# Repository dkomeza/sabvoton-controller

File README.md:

# sabvoton-controller

A controller for the sabvoton ebike esc.

## Pinout reference

```
---------------------------------------------------
| 01 | 02 | 03 | 04 | 05 | 06 | 07 | 08 | 09 | 10 |
---------------------------------------------------
| 11 | 12 | 13 | 14 | 15 | 16 | 17 | 18 | 19 | 20 |
---------------------------------------------------
| 21 | 22 | 23 | 24 | 25 | 26 | 27 | 28 | 29 | 30 |
---------------------------------------------------
```

- 01: speed (0V - Battery voltage)
- 02: programming (brown-blue)
- 03: low speed (controlled by gnd)
- 04: high speed (controlled by gnd)
- 05: brake (controlled by gnd)
- 06: service (unused)
- 07: empty
- 08: 5V
- 09: 5V square hall sensor (speedometer)
- 10: empty
- 11: battery voltage
- 12: programming (blue-yellow)
- 13: programming (green-black)
- 14: programming (red-black)
- 15: brake (controlled by 12v)
- 16: reverse (controlled by gnd)
- 17: gnd
- 18: gnd
- 19: throttle (0V - 5V)?
- 20: ignition (controlled by battery voltage)
- 21: engine phase (anti-theft)
- 22: empty
- 23: regen (controlled by gnd)
- 24: soft-start (connected to 26)
- 25: cruise control (controlled by gnd)
- 26: soft-start (connected to 24)
- 27: gnd
- 28: gnd
- 29: alarm (controlled by gnd)
- 30: service (unused)

## Working with the controller

### Connectors

- [x] 1: programming connector (same as the original)
- [x] 2: usb connector (for programming the arduino)

### Functions:

- [x] 1: set current gear (low, mid, high) - pins 03, 04
- [x] 2: set motor power based on the torque sensor input - pin 19
- [x] 3: read battery voltage - pin 11
- [x] 4: turn controller on/off - pin 20
- [x] 5: enable/disable soft start - pins 24, 26
- [x] 6: get engine temperature - white wire
- [x] 7: get engine rpm - white wire
- [x] 8: get controller temperature - additional sensor
- [x] 9: get battery temperature - additional sensor
- [x] 10: send data to the display - additional display
- [x] 11: get data from the display - additional display

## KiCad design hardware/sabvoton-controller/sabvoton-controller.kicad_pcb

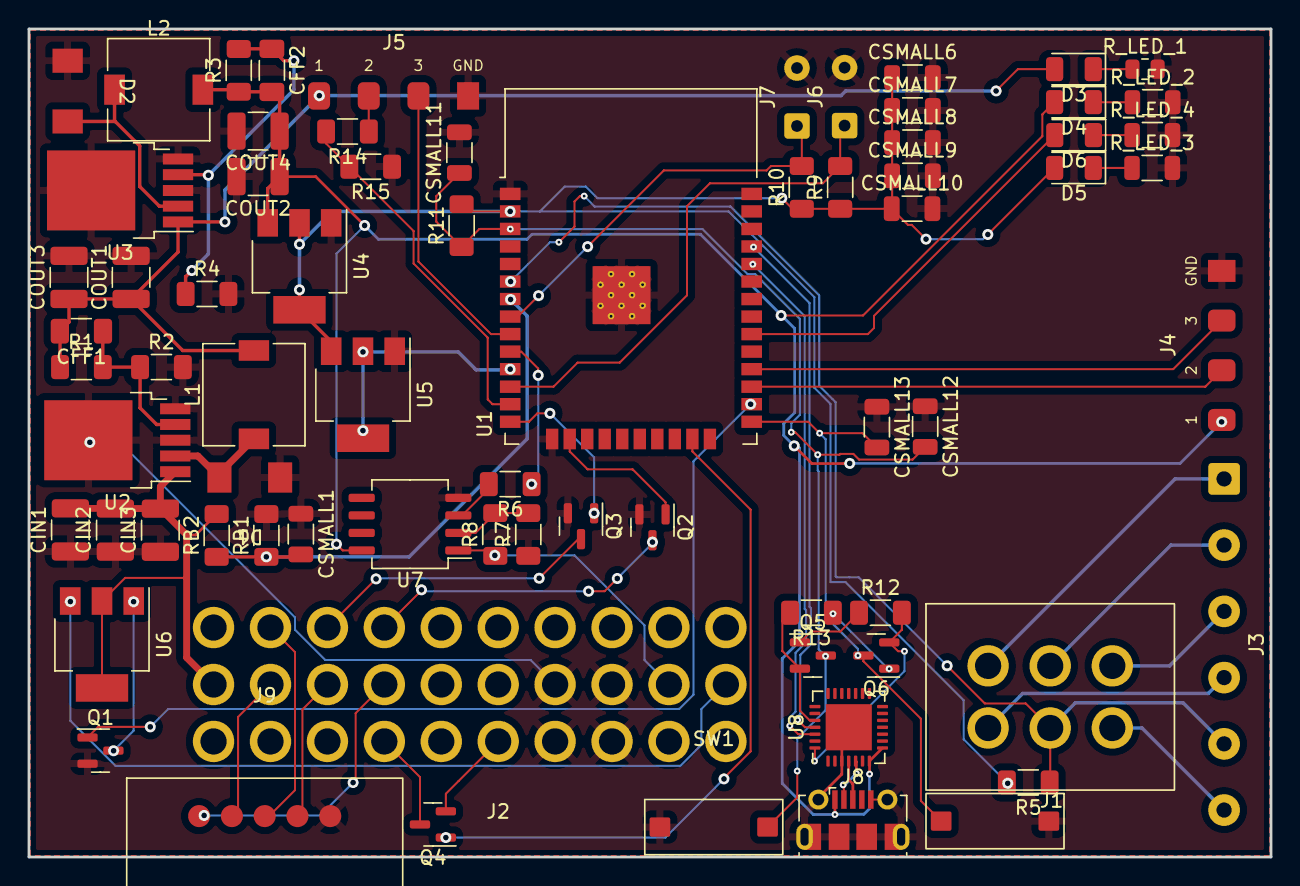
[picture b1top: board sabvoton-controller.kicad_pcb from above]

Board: 2 copper layers, 90.0 x 60.0 mm, 72 parts (0 on the bottom side), 57 nets.

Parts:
CFF1, CFF2: C; C_1206_3216Metric_Pad1.33x1.80mm_HandSolder
CIN1, CIN2, CIN3: C; C_1210_3225Metric_Pad1.33x2.70mm_HandSolder
COUT1, COUT2, COUT3, COUT4: C; C_1210_3225Metric_Pad1.33x2.70mm_HandSolder
CSMALL1, CSMALL6, CSMALL7, CSMALL8, CSMALL9, CSMALL10, CSMALL11, CSMALL12, CSMALL13: C; C_1206_3216Metric
D1, D2: S310; S2M
D3: 12V; LED_1206_3216Metric
D4: 5V; LED_1206_3216Metric
D5: 3.3V; LED_1206_3216Metric
D6: ESP_ON; LED_1206_3216Metric
J1: CONTROLLER_HALL; HALL_2x6
J2: CONN_MAIN; MAIN_3x10
J3: ENGINE_HALL; SolderWire-0.5sqmm_1x06_P4.8mm_D0.9mm_OD2.3mm
J4: DISPLAY_CONNECTOR; SolderWire-1x4-buttons
J5: TORQUE_SENSOR_CONNECTOR; SolderWire-1x4-buttons
J6: CONTROLLER_THERMISTOR_CONNECTOR; SolderWire-0.25sqmm_1x02_P4.2mm_D0.65mm_OD1.7mm
J7: BATTERY_THERMISTOR_CONNECTOR; SolderWire-0.25sqmm_1x02_P4.2mm_D0.65mm_OD1.7mm
J8: USB_B_Micro; USB_Micro-B_Molex-105017-0001
J9: PROGRAMMING_CONN; Pogramming_1x5
L1, L2: L; L_7.3x7.3_H3.5
Q1, Q2, Q3, Q4: BSS123; SOT-23
Q5, Q6: MMBT3904; SOT-23
R1: 86K; R_1206_3216Metric_Pad1.30x1.75mm_HandSolder
R2, R4, R5, R6, R9, R10, R11, R12, R13, R15: 10K; R_1206_3216Metric_Pad1.30x1.75mm_HandSolder
R3: 30K; R_1206_3216Metric_Pad1.30x1.75mm_HandSolder
R7, R8: 1K; R_1206_3216Metric_Pad1.30x1.75mm_HandSolder
R14: 33K; R_1206_3216Metric_Pad1.30x1.75mm_HandSolder
RB1: 56k; R_1206_3216Metric_Pad1.30x1.75mm_HandSolder
RB2: 1M; R_1206_3216Metric_Pad1.30x1.75mm_HandSolder
R_LED_1: 600; R_0805_2012Metric
R_LED_2: 130; R_1206_3216Metric
R_LED_3, R_LED_4: 20; R_1206_3216Metric
SW1, SW2: SW_Push; BUTTON_SW
U1: ESP32-WROOM-32
U2: BUCK_12V; TO-252-5_TabPin3
U3: BUCK_5V; TO-252-5_TabPin3
U4: NCP1117-3.3_SOT223; SOT-223-3_TabPin2
U5: LM1117-1.8; SOT-223-3_TabPin2
U6: BTS4140N; SOT-223-3_TabPin2
U7: LM358; SO-8_5.3x6.2mm_P1.27mm
U8: CP2102N-Axx-xQFN28; QFN-28-1EP_5x5mm_P0.5mm_EP3.35x3.35mm

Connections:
1.8V: U1.11 (IO26), U5.2 (VO)
3.3V: CSMALL6.1, CSMALL7.1, CSMALL8.1, CSMALL9.1, CSMALL10.1, D5.2 (A), R5.2, R9.1, R10.1, R11.2, U1.2 (VDD), U4.2 (VO), U5.3 (VI)
5V: CFF2.2, COUT2.1, COUT4.1, D4.2 (A), J4.1, J8.1 (VBUS), L2.2, R3.1, U4.3 (VI), U7.8 (VCC), U8.7 (VREGIN), U8.8 (VBUS)
12V: CFF1.2, COUT1.1, COUT3.1, D3.2 (A), J5.1, L1.2, R1.1, U3.1 (VIN)
B+: CIN1.2, CIN2.2, CIN3.2, J2.11, RB2.2, U2.1 (VIN), U6.2 (Vbb)
B-: CIN1.1, CIN2.1, CIN3.1, COUT1.2, COUT2.2, COUT3.2, COUT4.2, CSMALL1.1, CSMALL6.2, CSMALL7.2, CSMALL8.2, CSMALL9.2, CSMALL10.2, CSMALL11.2, CSMALL12.1, CSMALL13.1, D1.2 (A2), D2.2 (A2), J2.17, J2.18, J2.27, J2.28, J4.4, J5.4, J6.2, J7.2, J8.5 (GND), J8.6 (Shield), J9.5, Q1.2 (S), Q2.2 (S), Q3.2 (S), R2.2, R4.2, R7.1, R15.1, RB1.2, R_LED_1.2, R_LED_2.2, R_LED_3.2, R_LED_4.2, SW1.1, SW2.1, U1.1 (GND), U1.15 (GND), U1.38 (GND), U1.39 (GND), U2.3 (GND), U2.5 (EN), U3.3 (GND), U3.5 (EN), U4.1 (GND), U5.1 (GND), U7.4 (GND), U8.3 (GND), U8.29 (GND)
BATTERY_TEMP: J7.1, R10.2, U1.8 (IO32)
BATTERY_VOLTAGE: CSMALL1.2, RB1.1, RB2.1, U1.7 (IO35)
BOOT: CSMALL13.2, Q6.3 (C), SW2.2, U1.25 (IO0)
CONTROLLER_TEMP: J6.1, R9.2, U1.12 (IO27)
DISPLAY_RX: J4.2, U1.27 (IO16)
DISPLAY_TX: J4.3, U1.28 (IO17)
EN: CSMALL11.1, CSMALL12.2, Q5.3 (C), R11.1, SW1.2, U1.3 (EN)
ENGINE_SENSOR: J1.5, J3.5, R5.1, U1.6 (IO34)
GEAR_HIGH: J2.4, Q2.3 (D)
GEAR_LOW: J2.3, Q3.3 (D)
IGNITION: J2.20, U6.3 (OUT)
LED_ON: D6.2 (A), U1.30 (IO18)
unnamed: CFF1.1, R1.2, R2.1, U2.4 (FB)
unnamed: CFF2.1, R3.2, R4.1, U3.4 (FB)
unnamed: D1.1 (A1), L1.1, U2.2 (SW)
unnamed: D2.1 (A1), L2.1, U3.2 (SW)
unnamed: D3.1 (K), R_LED_1.1
unnamed: D4.1 (K), R_LED_2.1
unnamed: D5.1 (K), R_LED_3.1
unnamed: D6.1 (K), R_LED_4.1
unnamed: J1.1, J3.1
unnamed: J1.2, J3.2
unnamed: J1.3, J3.3
unnamed: J1.4, J3.4
unnamed: J1.6, J3.6
unnamed: J8.2 (D-), U8.5 (D-)
unnamed: J8.3 (D+), U8.4 (D+)
unnamed: Q1.3 (D), U6.1 (IN)
unnamed: Q5.1 (B), R12.1
unnamed: Q5.2 (E), R13.2, U8.24 (~RTS)
unnamed: Q6.1 (B), R13.1
unnamed: Q6.2 (E), R12.2, U8.28 (~DTR)
unnamed: R6.2, U7.3 (IN_A_+)
unnamed: R7.2, R8.2, U7.2 (IN_A_-)
PAS_SIGNAL: J5.2, R14.1
PAS_SIGNAL_LOW: R14.2, R15.2, U1.13 (IO14)
POWER_SWITCH: Q1.1 (G), U1.26 (IO4)
PROGRAMMING_BB: J2.2, J9.3
PROGRAMMING_BY: J2.12, J9.2
PROGRAMMING_GB: J2.13, J9.4
PROGRAMMING_RB: J2.14, J9.1
RXD: U1.35 (TXD0/IO1), U8.25 (RXD)
SOFT_START_A: J2.24, Q4.3 (D)
SOFT_START_B: J2.26, Q4.2 (S)
SWITCH_HIGH: Q2.1 (G), U1.16 (IO13)
SWITCH_LOW: Q3.1 (G), U1.14 (IO12)
SWITCH_SOFT_START: Q4.1 (G), U1.23 (IO15)
THROTTLE: J2.19, R8.1, U7.1 (OUT_A)
THROTTLE_OUTPUT: R6.1, U1.10 (IO25)
TORQUE_OUTPUT: J5.3, U1.9 (IO33)
TXD: U1.34 (RXD0/IO3), U8.26 (TXD)

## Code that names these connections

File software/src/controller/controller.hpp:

#ifndef CONTROLLER_H
#define CONTROLLER_H

#include <Arduino.h>

#include "../data/data.hpp"
#include "../settings/settings.hpp"

#define POWER_PIN 4

#define GEAR_LOW_PIN 12
#define GEAR_HIGH_PIN 13

#define THROTTLE_PIN 25

#define SOFT_START_PIN 15

#define MAX_THROTTLE 188

class Controller
{
public:
    void update();

private:
    int gear = 0;
    int throttle = 0;
    bool power = false;
    bool softStart = true;

    int getThrottleValue(int throttle);

    void setPower(bool power);
    void setGear(int gear);
    void setThrottle(int throttle);
    void setSoftStart(bool softStart);
};

extern Controller controller;

#endif

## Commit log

2023-04-07 Added controller pinout
2023-04-07 Added project philosophy and goals
2023-04-09 Added controller connectors && microcontroller
2023-04-09 Added 12V conversion part
2023-04-09 Added 5V conversion part
2023-04-09 Added 3.3V conversion
2023-04-09 Added 1.8V converter (voltage reference)
2023-04-09 Connect negative battery to gnd
2023-04-09 Added more controller connections
2023-04-09 Added power to the ESP32
2023-04-10 Added power switch circuit
2023-04-10 Connect power switch to the esp
2023-04-10 Added battery voltage input
2023-04-10 Added engine temperature & speed sensor
2023-04-10 Added gear switch
2023-04-10 Added throttle output
2023-04-10 Added torque sensor connection
2023-04-10 Added soft start switch
2023-04-10 Added battery & controller thermistor connections
2023-04-10 Added new function
2023-04-10 Added task list
2023-04-12 Added USB connector
2023-04-15 README update
2023-04-16 Added programing connector
2023-04-16 Update progress list
2023-05-05 Finished PCB design
2023-05-16 Add gitignore
2023-05-16 :tada: Init PlatformIO project.
2023-05-16 :sparkles: Add function files
2023-05-16 :sparkles: Add Controller class implementation
2023-05-16 :sparkles: Add controller power switch
2023-05-16 :sparkles: Add controller gear selection
2023-05-16 :bug: Fix incorrect power pin
2023-05-16 :sparkles: Add throttle output
2023-05-16 :sparkles: Add soft start switch
2023-05-16 :sparkles: Add voltage reading
2023-05-16 :sparkles: Add temperature sensor reading
2023-06-22 :art: Change folder names
2023-06-22 :art: Move KiCad files directly to the hardware folder.
2023-06-22 :sparkles: Add OTA function
2023-06-22 :sparkles: Add OTA to the main loop
2023-06-22 :sparkles: Add basic main loop setup
2023-06-22 :sparkles: Add data class
2023-06-23 :sparkles: Add data definitions
2023-06-23 :sparkles: Send data to the display
2023-06-23 :sparkles: Receive data from the display
2023-06-23 :hammer: Move getVoltage function to IO class
2023-06-23 :sparkles: Create main controller loop
2023-06-24 :sparkles: Read torque sensor input
2023-07-21 :bug: Fix ADC2 not working when WiFi is on
2023-09-12 :zap: Major updates
